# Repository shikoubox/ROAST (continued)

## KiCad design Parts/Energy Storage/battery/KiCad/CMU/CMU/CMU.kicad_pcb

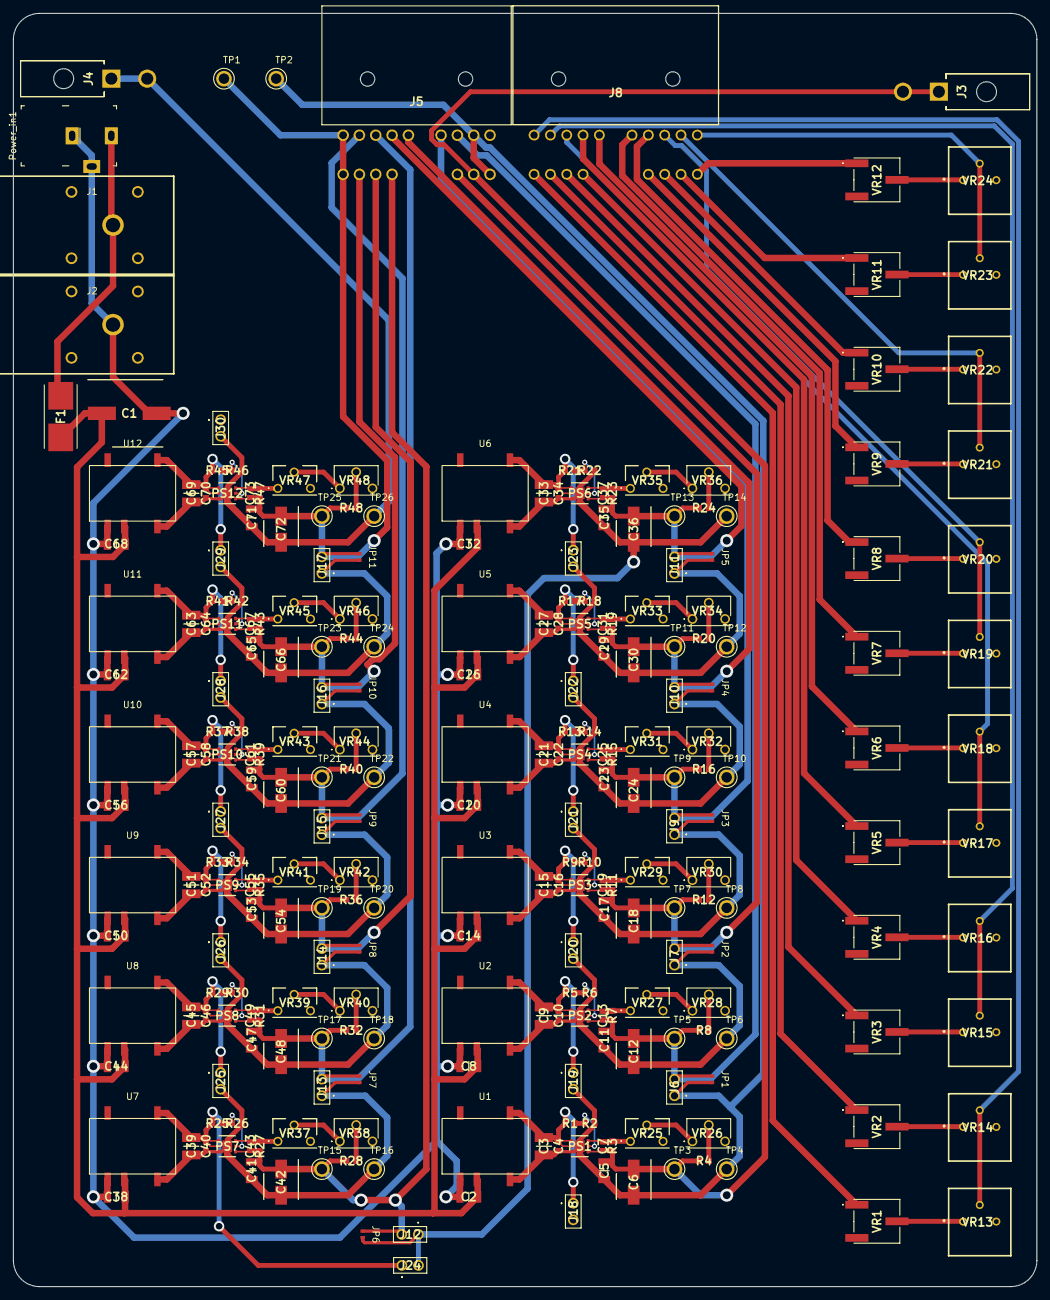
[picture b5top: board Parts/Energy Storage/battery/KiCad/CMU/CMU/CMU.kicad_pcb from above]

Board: 4 copper layers, 156.8 x 195.0 mm, 262 parts (0 on the bottom side), 117 nets.

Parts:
C1: 865080657018; CAPAE1030X1050N
C2, C8, C14, C20, C26, C32, C38, C44, C50, C56, C62, C68: 885012208094; CAPC3216X180N
C3, C9, C15, C21, C27, C33, C39, C45, C51, C57, C63, C69: 885012209073; CAPC3225X280N
C4, C10, C16, C22, C28, C34, C40, C46, C52, C58, C64, C70: 885012206095; CAPC1608X87N
C5, C11, C17, C23, C29, C35, C41, C47, C53, C59, C65, C71: 885012208069; CAPC3216X180N
C6, C12, C18, C24, C30, C36, C42, C48, C54, C60, C66, C72: 875105242010; CAPAE530X550N
C7, C13, C19, C25, C31, C37, C43, C49, C55, C61, C67, C73: 885012006053; CAPC1608X87N
F1: 015406.3DR; 0154063DR
J1, J2: FCR7350R
J3, J4: 649002227222
J5: IL-AG5-16P-D3L2-A; ILAG516PD3L2A
J6, J7, J9, J10, J11, J12, J13, J14, J15, J16, J17, J18, J19, J20, J21, J22, J23, J24, J25, J26, J27, J28, J29, J30: 77311-101-02LF; 7731110102LF
J8: IL-AG5-18P-D3L2; ILAG518PD3L2
JP1, JP2, JP3, JP4, JP5, JP6, JP7, JP8, JP9, JP10, JP11: SolderJumper_2_Open; solder_jumper
PS1, PS2, PS3, PS4, PS5, PS6, PS7, PS8, PS9, PS10, PS11, PS12: 171010502
Power_in1: PJ-102A; Barrel_Jack_5.5mmODx2.1mmID_PJ-102A
R1, R2, R3, R5, R6, R7, R9, R10, R11, R13, R14, R15, R17, R18, R19, R21, R22, R23, R25, R26, R27, R29, R30, R31, R33, R34, R35, R37, R38, R39, R41, R42, R43, R45, R46, R47: CRT0603-FZ-1003ELF; RESC1608X60N
R4, R8, R12, R16, R20, R24, R28, R32, R36, R40, R44, R48: RT0603FRE0720KL; RESC1608X55N
TP1, TP2, TP3, TP4, TP5, TP6, TP7, TP8, TP9, TP10, TP11, TP12, TP13, TP14, TP15, TP16, TP17, TP18, TP19, TP20, TP21, TP22, TP23, TP24, TP25, TP26: 5013; TESTPOINT_5013
U1, U2, U3, U4, U5, U6, U7, U8, U9, U10, U11, U12: 1769405341
VR1, VR2, VR3, VR4, VR5, VR6, VR7, VR8, VR9, VR10, VR11, VR12: 3361P-1-504GLF; 3361P1253GLF
VR13, VR14, VR15, VR16, VR17, VR18, VR19, VR20, VR21, VR22, VR23, VR24: 3362P-1-103TLF; 3296P-1-103
VR25, VR27, VR29, VR31, VR33, VR35, VR37, VR39, VR41, VR43, VR45, VR47: PV37W104C01B00
VR26, VR28, VR30, VR32, VR34, VR36, VR38, VR40, VR42, VR44, VR46, VR48: PV37W102C01B00

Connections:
/CMU1/IN+: C1.1, C2.1, C8.1, C14.1, C20.1, C26.1, C32.1, C38.1, C44.1, C50.1, C56.1, C62.1, C68.1, F1.2, U1.2 (+VIN), U2.2 (+VIN), U3.2 (+VIN), U4.2 (+VIN), U5.2 (+VIN), U6.2 (+VIN), U7.2 (+VIN), U8.2 (+VIN), U9.2 (+VIN), U10.2 (+VIN), U11.2 (+VIN), U12.2 (+VIN)
/CMU1/IN-: C1.2, C2.2, C8.2, C14.2, C20.2, C26.2, C32.2, C38.2, C44.2, C50.2, C56.2, C62.2, C68.2, J2.5, Power_in1.2, Power_in1.3, U1.1 (-VIN), U2.1 (-VIN), U3.1 (-VIN), U4.1 (-VIN), U5.1 (-VIN), U6.1 (-VIN), U7.1 (-VIN), U8.1 (-VIN), U9.1 (-VIN), U10.1 (-VIN), U11.1 (-VIN), U12.1 (-VIN)
/CMU1/ISO+: C3.1, C4.1, J18.1, PS1.4 (VIN), PS1.5 (EN), R1.1, U1.5 (+VOUT)
/CMU2/ISO+: C9.1, C10.1, J19.1, PS2.4 (VIN), PS2.5 (EN), R5.1, U2.5 (+VOUT)
/CMU2/OUT-: C9.2, C10.2, C11.2, C12.2, J7.1, J20.2, JP2.2 (B), PS2.6 (PGND), PS2.7 (EP), R6.2, TP6.1, U2.4 (-VOUT)
/CMU3/ISO+: C15.1, C16.1, J20.1, PS3.4 (VIN), PS3.5 (EN), R9.1, U3.5 (+VOUT)
/CMU3/OUT-: C15.2, C16.2, C17.2, C18.2, J9.1, J21.2, JP3.2 (B), PS3.6 (PGND), PS3.7 (EP), R10.2, TP8.1, U3.4 (-VOUT)
/CMU4/ISO+: C21.1, C22.1, J21.1, PS4.4 (VIN), PS4.5 (EN), R13.1, U4.5 (+VOUT)
/CMU4/OUT-: C21.2, C22.2, C23.2, C24.2, J10.1, J22.2, JP4.2 (B), PS4.6 (PGND), PS4.7 (EP), R14.2, TP10.1, U4.4 (-VOUT)
/CMU5/ISO+: C27.1, C28.1, J22.1, PS5.4 (VIN), PS5.5 (EN), R17.1, U5.5 (+VOUT)
/CMU5/OUT-: C27.2, C28.2, C29.2, C30.2, J11.1, J23.2, JP5.2 (B), PS5.6 (PGND), PS5.7 (EP), R18.2, TP12.1, U5.4 (-VOUT)
/CMU6/ISO+: C33.1, C34.1, J23.1, PS6.4 (VIN), PS6.5 (EN), R21.1, U6.5 (+VOUT)
/CMU6/OUT-: C33.2, C34.2, C35.2, C36.2, J12.1, J24.2, JP6.2 (B), PS6.6 (PGND), PS6.7 (EP), R22.2, TP14.1, U6.4 (-VOUT)
/CMU7/ISO+: C39.1, C40.1, J24.1, PS7.4 (VIN), PS7.5 (EN), R25.1, U7.5 (+VOUT)
/CMU7/OUT-: C39.2, C40.2, C41.2, C42.2, J13.1, J25.2, JP7.2 (B), PS7.6 (PGND), PS7.7 (EP), R26.2, TP16.1, U7.4 (-VOUT)
/CMU8/ISO+: C45.1, C46.1, J25.1, PS8.4 (VIN), PS8.5 (EN), R29.1, U8.5 (+VOUT)
/CMU8/OUT-: C45.2, C46.2, C47.2, C48.2, J14.1, J26.2, JP8.2 (B), PS8.6 (PGND), PS8.7 (EP), R30.2, TP18.1, U8.4 (-VOUT)
/CMU9/ISO+: C51.1, C52.1, J26.1, PS9.4 (VIN), PS9.5 (EN), R33.1, U9.5 (+VOUT)
/CMU9/OUT-: C51.2, C52.2, C53.2, C54.2, J15.1, J27.2, JP9.2 (B), PS9.6 (PGND), PS9.7 (EP), R34.2, TP20.1, U9.4 (-VOUT)
/CMU10/ISO+: C57.1, C58.1, J27.1, PS10.4 (VIN), PS10.5 (EN), R37.1, U10.5 (+VOUT)
/CMU10/OUT-: C57.2, C58.2, C59.2, C60.2, J16.1, J28.2, JP10.2 (B), PS10.6 (PGND), PS10.7 (EP), R38.2, TP22.1, U10.4 (-VOUT)
/CMU11/ISO+: C63.1, C64.1, J28.1, PS11.4 (VIN), PS11.5 (EN), R41.1, U11.5 (+VOUT)
/CMU11/OUT-: C63.2, C64.2, C65.2, C66.2, J17.1, J29.2, JP11.2 (B), PS11.6 (PGND), PS11.7 (EP), R42.2, TP24.1, U11.4 (-VOUT)
/CMU12/ISO+: C69.1, C70.1, J29.1, PS12.4 (VIN), PS12.5 (EN), R45.1, U12.5 (+VOUT)
/CMU12/ISO-: C69.2, C70.2, C71.2, C72.2, J4.1, J4.2, J30.2, PS12.6 (PGND), PS12.7 (EP), R46.2, TP26.1, U12.4 (-VOUT)
/GND_NTC_1_2: J8.18, VR23.2 (WIPER), VR24.2 (WIPER)
/GND_NTC_3_4: J8.17, VR21.2 (WIPER), VR22.2 (WIPER)
/GND_NTC_5_6: J8.16, VR19.2 (WIPER), VR20.2 (WIPER)
/GND_NTC_7_8: J8.11, VR17.2 (WIPER), VR18.2 (WIPER)
/GND_NTC_9_10: J8.10, VR15.2 (WIPER), VR16.2 (WIPER)
/GND_NTC_11_12: J8.9, VR13.2 (WIPER), VR14.2 (WIPER)
CMU1+: C5.1, C6.1, C7.1, J3.1, J3.2, J5.6, PS1.1 (VOUT), R3.2, R4.2, TP3.1
CMU1-: C3.2, C4.2, C5.2, C6.2, J5.7, J5.15, J6.1, J19.2, JP1.2 (B), PS1.6 (PGND), PS1.7 (EP), R2.2, TP2.1, TP4.1, U1.4 (-VOUT)
CMU2+: C11.1, C12.1, C13.1, J5.14, J6.2, JP1.1 (A), PS2.1 (VOUT), R7.2, R8.2, TP5.1
CMU3+: C17.1, C18.1, C19.1, J5.5, J7.2, JP2.1 (A), PS3.1 (VOUT), R11.2, R12.2, TP7.1
CMU4+: C23.1, C24.1, C25.1, J5.13, J9.2, JP3.1 (A), PS4.1 (VOUT), R15.2, R16.2, TP9.1
CMU5+: C29.1, C30.1, C31.1, J5.12, J10.2, JP4.1 (A), PS5.1 (VOUT), R19.2, R20.2, TP11.1
CMU6+: C35.1, C36.1, C37.1, J5.11, J11.2, JP5.1 (A), PS6.1 (VOUT), R23.2, R24.2, TP13.1
CMU7+: C41.1, C42.1, C43.1, J5.4, J12.2, JP6.1 (A), PS7.1 (VOUT), R27.2, R28.2, TP15.1
CMU8+: C47.1, C48.1, C49.1, J5.10, J13.2, JP7.1 (A), PS8.1 (VOUT), R31.2, R32.2, TP17.1
CMU9+: C53.1, C54.1, C55.1, J5.3, J14.2, JP8.1 (A), PS9.1 (VOUT), R35.2, R36.2, TP19.1
CMU10+: C59.1, C60.1, C61.1, J5.9, J15.2, JP9.1 (A), PS10.1 (VOUT), R39.2, R40.2, TP21.1
CMU11+: C65.1, C66.1, C67.1, J5.2, J16.2, JP10.1 (A), PS11.1 (VOUT), R43.2, R44.2, TP23.1
CMU12+: C71.1, C72.1, C73.1, J5.1, J5.8, J17.2, JP11.1 (A), PS12.1 (VOUT), R47.2, R48.2, TP1.1, TP25.1
unnamed: C7.2, PS1.3 (FB), R3.1, VR25.1 (CCW)
unnamed: C13.2, PS2.3 (FB), R7.1, VR27.1 (CCW)
unnamed: C19.2, PS3.3 (FB), R11.1, VR29.1 (CCW)
unnamed: C25.2, PS4.3 (FB), R15.1, VR31.1 (CCW)
unnamed: C31.2, PS5.3 (FB), R19.1, VR33.1 (CCW)
unnamed: C37.2, PS6.3 (FB), R23.1, VR35.1 (CCW)
unnamed: C43.2, PS7.3 (FB), R27.1, VR37.1 (CCW)
unnamed: C49.2, PS8.3 (FB), R31.1, VR39.1 (CCW)
unnamed: C55.2, PS9.3 (FB), R35.1, VR41.1 (CCW)
unnamed: C61.2, PS10.3 (FB), R39.1, VR43.1 (CCW)
unnamed: C67.2, PS11.3 (FB), R43.1, VR45.1 (CCW)
unnamed: C73.2, PS12.3 (FB), R47.1, VR47.1 (CCW)
unnamed: F1.1, J1.5, Power_in1.1
unnamed: J8.1, VR1.1 (CCW)
unnamed: J8.2, VR2.1 (CCW)
unnamed: J8.3, VR3.1 (CCW)
unnamed: J8.4, VR4.1 (CCW)
unnamed: J8.5, VR9.1 (CCW)
unnamed: J8.6, VR10.1 (CCW)
unnamed: J8.7, VR11.1 (CCW)
unnamed: J8.8, VR12.1 (CCW)
unnamed: J8.12, VR5.1 (CCW)
unnamed: J8.13, VR6.1 (CCW)
unnamed: J8.14, VR7.1 (CCW)
unnamed: J8.15, VR8.1 (CCW)
unnamed: PS1.2 (MODE), R1.2, R2.1
unnamed: PS2.2 (MODE), R5.2, R6.1
unnamed: PS3.2 (MODE), R9.2, R10.1
unnamed: PS4.2 (MODE), R13.2, R14.1
unnamed: PS5.2 (MODE), R17.2, R18.1
unnamed: PS6.2 (MODE), R21.2, R22.1
unnamed: PS7.2 (MODE), R25.2, R26.1
unnamed: PS8.2 (MODE), R29.2, R30.1
unnamed: PS9.2 (MODE), R33.2, R34.1
unnamed: PS10.2 (MODE), R37.2, R38.1
unnamed: PS11.2 (MODE), R41.2, R42.1
unnamed: PS12.2 (MODE), R45.2, R46.1
unnamed: R4.1, VR26.2 (WIPER)
unnamed: R8.1, VR28.2 (WIPER)
unnamed: R12.1, VR30.2 (WIPER)
unnamed: R16.1, VR32.2 (WIPER)
unnamed: R20.1, VR34.2 (WIPER)
unnamed: R24.1, VR36.2 (WIPER)
unnamed: R28.1, VR38.2 (WIPER)
unnamed: R32.1, VR40.2 (WIPER)
unnamed: R36.1, VR42.2 (WIPER)
unnamed: R40.1, VR44.2 (WIPER)
unnamed: R44.1, VR46.2 (WIPER)
unnamed: R48.1, VR48.2 (WIPER)
unnamed: VR1.2 (WIPER), VR13.1 (CCW)
unnamed: VR10.2 (WIPER), VR22.1 (CCW)
unnamed: VR11.2 (WIPER), VR23.1 (CCW)
unnamed: VR12.2 (WIPER), VR24.1 (CCW)
unnamed: VR2.2 (WIPER), VR14.1 (CCW)
unnamed: VR3.2 (WIPER), VR15.1 (CCW)
unnamed: VR4.2 (WIPER), VR16.1 (CCW)
unnamed: VR5.2 (WIPER), VR17.1 (CCW)
unnamed: VR6.2 (WIPER), VR18.1 (CCW)
unnamed: VR7.2 (WIPER), VR19.1 (CCW)
unnamed: VR8.2 (WIPER), VR20.1 (CCW)
unnamed: VR9.2 (WIPER), VR21.1 (CCW)
unnamed: VR25.2 (WIPER_), VR26.1 (CCW)
unnamed: VR27.2 (WIPER_), VR28.1 (CCW)
unnamed: VR29.2 (WIPER_), VR30.1 (CCW)
unnamed: VR31.2 (WIPER_), VR32.1 (CCW)
unnamed: VR33.2 (WIPER_), VR34.1 (CCW)
unnamed: VR35.2 (WIPER_), VR36.1 (CCW)
unnamed: VR37.2 (WIPER_), VR38.1 (CCW)
unnamed: VR39.2 (WIPER_), VR40.1 (CCW)
unnamed: VR41.2 (WIPER_), VR42.1 (CCW)
unnamed: VR43.2 (WIPER_), VR44.1 (CCW)
unnamed: VR45.2 (WIPER_), VR46.1 (CCW)
unnamed: VR47.2 (WIPER_), VR48.1 (CCW)

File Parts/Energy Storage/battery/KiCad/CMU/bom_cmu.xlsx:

Id | Designator | Package | Quantity | Designation | Manufacturer | Price/unit [€] | Total [€] | AVAL. ATTOW. | Link
1 | R32,R28,R8,R44,R40,R16,R48,R36,R12,R4,R20,R24 | RESC1608X55N | 12 | RT0603FRE0720KL | x | 1.6E-2 | 0.192 | 53684 | https://www.mouser.dk/ProductDetail/YAGEO/RT0603FRE0720KL?qs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
2 | H4,H1,H2,H3 | MountingHole_3.2mm_M3_ISO7380_Pad | 4 | MountingHole |  | 0 | 0 | PCB design
3 | VR27,VR33,VR41,VR39,VR37,VR1,VR47,VR35,VR31,VR29,VR45,VR43 | PV37W104C01B00 | 12 | PV37W104C01B00 | x | 1.57 | 18.84 | 19364 | https://www.mouser.dk/ProductDetail/Bourns/PV37W104C01B00?qs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
4 | VR25,VR22,VR15,VR17,VR26,VR23,VR24,VR19,VR21,VR18,VR20,VR16 | PV37W103C01B00 | 12 | PV37W103C01B00 | x | 1.58 | 18.96 | 2223 | https://www.mouser.dk/ProductDetail/Bourns/PV37W103C01B00?qs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
5 | JP3,JP7,JP5,JP8,JP10,JP11,JP9,JP6,JP1,JP4,JP2 | solder_jumper | 11 | SolderJumper_2_Open |  | 0 | 0 | PCB design
6 | J28,J19,J25,J5,J27,J10,J24,J26,J11,J6,J23,J14,J20,J9,J4,J12,J21,J22,J7,J16,J15,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 | 7731110102LF | 24 | 77311-101-02LF | x | 0.16500000000000001 | 3.96 | 5243 | https://www.mouser.dk/ProductDetail/Amphenol-FCI/77311-101-0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
7 | C3,C64,C52,C22,C40,C28,C16,C58,C10,C70,C46,C34 | CAPC1608X87N | 12 | 885012206095 | x | 5.2999999999999999E-2 | 0.63600000000000001 | 96611 | https://www.mouser.dk/ProductDetail/Wurth-Elektronik/8850122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
8 | C9,C39,C2,C51,C15,C21,C27,C33,C57,C63,C69,C45 | CAPC3225X280N | 12 | 885012209073 | x | 1.5920000000000001 | 19.103999999999999 | 1915 | https://www.digikey.dk/en/products/detail/w%C3%BCrth-elektro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
9 | TP14,TP21,TP40,TP13,TP48,TP16,TP10,TP17,TP34,TP53,TP5,TP44,TP22,TP36,TP54,TP15,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 | TESTPOINT_5013 | 62 | 5013 | x | 0.26700000000000002 | 16.554000000000002 | 28911 | https://www.mouser.dk/ProductDetail/Keystone-Electronics/501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
10 | R31,R25,R35,R23,R2,R29,R11,R21,R15,R30,R22,R43,R26,R45,R1,R3,R47,R33,R42,R41,R4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 | RESC1608X60N | 36 | MCT06030C1003FP500 | x | 4.3999999999999997E-2 | 1.5839999999999999 | 69865 | https://www.digikey.dk/en/products/detail/vishay-beyschlag-d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
11 | C26,C32,C8,C62,C1,C44,C20,C50,C38,C14,C56,C68 | CAPC3216X180N | 12 | 885012208094 | x | 0.79100000000000004 | 9.4920000000000009 | 7413 | https://www.digikey.dk/en/products/detail/w%C3%BCrth-elektro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
12 | VR28,VR2,VR44,VR34,VR36,VR38,VR46,VR32,VR42,VR48,VR40,VR30 | PV37W102C01B00 | 12 | PV37W102C01B00 | x | 1.52 | 18.240000000000002 | 2268 | https://www.mouser.dk/ProductDetail/Bourns/PV37W102C01B00?qs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
13 | U3,U1,U10,U7,U12,U5,U6,U9,U8,U4,U11,U2 | 1769405341 | 12 | 1769405341 | x | 6.1680000000000001 | 74.016000000000005 | 417 | https://www.mouser.dk/ProductDetail/Wurth-Elektronik/1769405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
14 | C11,C23,C35,C59,C71,C4,C65,C53,C29,C41,C47,C17 | CAPC3216X180N | 12 | 885012208069 | x | 0.50900000000000001 | 6.1080000000000005 | 18083 | https://www.digikey.dk/en/products/detail/w%C3%BCrth-elektro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
15 | C42,C24,C66,C18,C72,C30,C60,C36,C48,C12,C5,C54 | CAPAE530X550N | 12 | 875105242010 | x | 0.46899999999999997 | 5.6280000000000001 | 2312 | https://www.digikey.dk/en/products/detail/w%C3%BCrth-elektro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
16 | C7 | CAPAE1030X1050N | 1 | 865080657018 | Wurth Elektronik | 0.84 | 0.84 | 77987 | https://www.digikey.dk/en/products/detail/w%C3%BCrth-elektro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
17 | C13,C55,C6,C49,C67,C19,C43,C31,C25,C61,C37,C73 | CAPC1608X87N | 12 | 885012006053 | x | 2.4E-2 | 0.28800000000000003 | 15365 | https://www.mouser.dk/ProductDetail/Wurth-Elektronik/8850120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
18 | J18,J17 | 649002227222 | 2 | 649002227222 | Wurth Elektronik | 1.27 | 2.54 | 2337 | https://www.mouser.dk/ProductDetail/Wurth-Elektronik/6490022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
 |  |  | 2 | 649002113322 | x | 0.17 | 0.34 | 4482 | https://www.digikey.dk/en/products/detail/w%C3%BCrth-elektro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
19 | PS12,PS3,PS2,PS1,PS10,PS11,PS8,PS4,PS5,PS7,PS9,PS6 | 171010502 | 12 | 171010502 | x | 4.4779999999999998 | 53.735999999999997 | 620 | https://www.digikey.dk/en/products/detail/w%C3%BCrth-elektro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
20 | VR6,VR7,VR12,VR4,VR3,VR9,VR5,VR14,VR11,VR13,VR8,VR10 | PV37W504C01B00 | 12 | PV37W504C01B00 | x | 0.81 | 9.7200000000000006 | 1755 | https://www.mouser.dk/ProductDetail/Bourns/PV37W504C01B00?qs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
21 | J3 | FCR7350B | 1 | FCR7350B | x | 4.8499999999999996 | 4.8499999999999996 | 806 | https://www.digikey.dk/en/products/detail/cliff-electronic-c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
22 | J1 | FCR7350R | 1 | FCR7350R | x | 4.8499999999999996 | 4.8499999999999996 | 5587 | https://www.digikey.dk/en/products/detail/cliff-electronic-c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
23 | Power_in1 | Barrel_Jack_5.5mmODx2.1mmID_PJ-102A | 1 | PJ-102A | x | 0.60499999999999998 | 0.60499999999999998 | 17619 | https://www.mouser.dk/ProductDetail/CUI-Devices/PJ-102A?qs=W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
24 | J2 | 64901629522 | 1 | 64901629522 | x | 1.87 | 1.87 | 90 | https://www.digikey.dk/en/products/detail/w%C3%BCrth-elektro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
 |  |  | 1 | 649016113322 | x | 0.63 | 0.63 | 315 | https://www.digikey.dk/en/products/detail/w%C3%BCrth-elektro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
25 | F1 | 0154063DR | 1 | 015406.3DR | x | 2.5 | 2.5 | 7949 | https://www.mouser.dk/ProductDetail/Littelfuse/015406.3DR?qs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
 |  |  | 5 | 045106.3MRL | x | 1.266 | 6.33 | 782 | https://www.digikey.dk/en/products/detail/littelfuse-inc/045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
26 | J30 | 64901829522 | 1 | 64901829522 | x | 1.99 | 1.99 | 63 | https://www.digikey.dk/en/products/detail/w%C3%BCrth-elektro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
 |  |  | 1 | 649018113322 | x | 0.7 | 0.7 | 140 | https://www.digikey.dk/en/products/detail/w%C3%BCrth-elektro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
 |  |  |  |  |  | Total | 285.10300000000007

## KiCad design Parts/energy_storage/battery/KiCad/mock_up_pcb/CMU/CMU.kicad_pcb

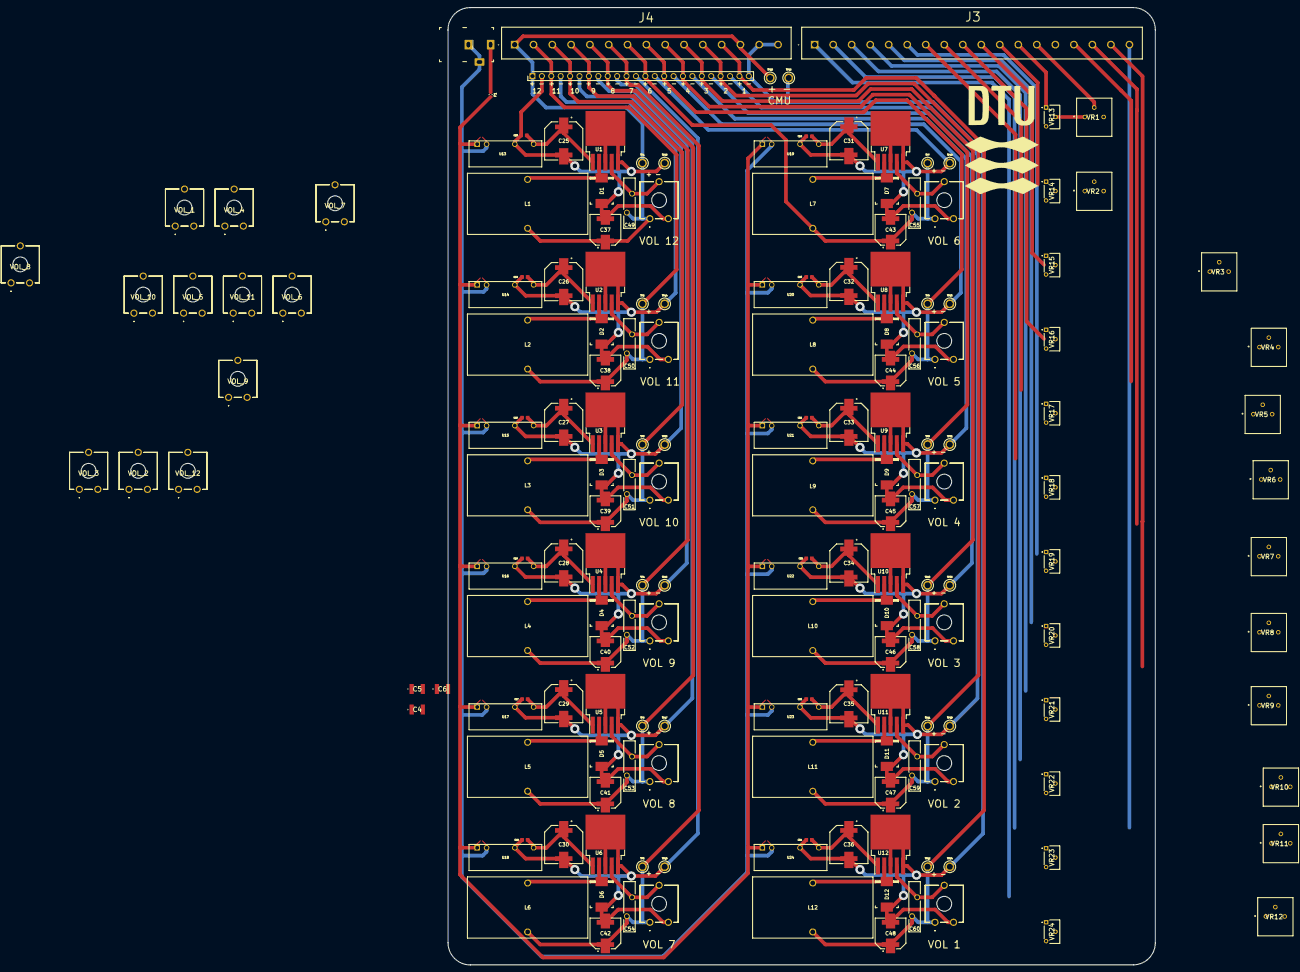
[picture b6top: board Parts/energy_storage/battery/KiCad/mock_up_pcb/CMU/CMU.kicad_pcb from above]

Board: 2 copper layers, 191.0 x 258.5 mm, 178 parts (0 on the bottom side), 93 nets.

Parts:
C4, C5, C6: C1210C225K1RACAUTO; C1210
C13, C14, C15, C16, C17, C18, C19, C20, C21, C22, C23, C24: 10u; CAPC1608X100N
C25, C26, C27, C28, C29, C30, C31, C32, C33, C34, C35, C36: 470u; CAP_EEETP1A471AV
C37, C38, C39, C40, C41, C42, C43, C44, C45, C46, C47, C48: 220u; CAP_EEETP1A221AV
C49, C50, C51, C52, C53, C54, C55, C56, C57, C58, C59, C60: 3.2n; FUSRB510W81L1358T310H1980
D1, D2, D3, D4, D5, D6, D7, D8, D9, D10, D11, D12: B540C-13-F; DO-214AB
F1: 0ABB-5000-TM; FUSE_0ABB-5000-TM
J3: 1755668
J4: 1755862
L1, L2, L3, L4, L5, L6, L7, L8, L9, L10, L11, L12: HCTI-100-7.0; IND_HCTI-68-7.7
Power_in1: PJ-102A; Barrel_Jack_5.5mmODx2.1mmID_PJ-102A
TP1, TP2, TP3, TP4, TP5, TP6, TP7, TP8, TP9, TP10, TP11, TP12, TP13, TP14, TP15, TP16, TP17, TP18, TP19, TP20, TP21, TP22, TP23, TP24, TP25, TP26: 5013; TESTPOINT_5013
U1, U2, U3, U4, U5, U6, U7, U8, U9, U10, U11, U12: LM2596S-ADJ; TO-263-5_TabPin3
U13, U14, U15, U16, U17, U18, U19, U20, U21, U22, U23, U24: PEM2-S12-S5-S; CONV_PEM2-S12-S5-S
VOL 1, VOL 2, VOL 3, VOL 4, VOL 5, VOL 6, VOL 7, VOL 8, VOL 9, VOL 10, VOL 11, VOL 12: PT10RV10-103A2020-PM-S; PT10RV10103A2020PMS
VOL_1, VOL_2, VOL_3, VOL_4, VOL_5, VOL_6, VOL_7, VOL_8, VOL_9, VOL_10, VOL_11, VOL_12: PT10RV10-103A2020-PM-S; PT10RV10103A2020PMS
VR1, VR2, VR3, VR4, VR5, VR6, VR7, VR8, VR9, VR10, VR11, VR12: 3362P-1-103TLF; 3296P-1-103
VR13, VR14, VR15, VR16, VR17, VR18, VR19, VR20, VR21, VR22, VR23, VR24: 64WR500KLF
Voltage_headers1: 77311-102-24LF; HDRV24W62P0X254_1X24_6096X240X858P

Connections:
/CMU_vol_1: C48.1, C60.2, J4.12, L12.2, TP12.1, VOL 1.A1 (CCW), VOL_1.A1 (CCW), Voltage_headers1.23
/CMU_vol_2: C47.1, C59.2, J4.11, L11.2, TP11.1, VOL 2.A1 (CCW), VOL_2.A1 (CCW), Voltage_headers1.21
/CMU_vol_3: C46.1, C58.2, J4.10, L10.2, TP10.1, VOL 3.A1 (CCW), VOL_3.A1 (CCW), Voltage_headers1.19
/CMU_vol_4: C45.1, C57.2, J4.9, L9.2, TP9.1, VOL 4.A1 (CCW), VOL_4.A1 (CCW), Voltage_headers1.17
/CMU_vol_5: C44.1, C56.2, J4.8, L8.2, TP8.1, VOL 5.A1 (CCW), VOL_5.A1 (CCW), Voltage_headers1.15
/CMU_vol_6: C43.1, C55.2, J4.7, L7.2, TP7.1, VOL 6.A1 (CCW), VOL_6.A1 (CCW), Voltage_headers1.13
/CMU_vol_7: C42.1, C54.2, J4.6, L6.2, TP6.1, VOL 7.A1 (CCW), VOL_7.A1 (CCW), Voltage_headers1.11
/CMU_vol_8: C41.1, C53.2, J4.5, L5.2, TP5.1, VOL 8.A1 (CCW), VOL_8.A1 (CCW), Voltage_headers1.9
/CMU_vol_9: C40.1, C52.2, J4.4, L4.2, TP4.1, VOL 9.A1 (CCW), VOL_9.A1 (CCW), Voltage_headers1.7
/CMU_vol_10: C39.1, C51.2, J4.3, L3.2, TP3.1, VOL 10.A1 (CCW), VOL_10.A1 (CCW), Voltage_headers1.5
/CMU_vol_11: C38.1, C50.2, J4.2, L2.2, TP2.1, VOL 11.A1 (CCW), VOL_11.A1 (CCW), Voltage_headers1.3
/CMU_vol_12: C37.1, C49.2, J4.1, J4.13, L1.2, TP1.1, TP25.1, VOL 12.A1 (CCW), VOL_12.A1 (CCW), Voltage_headers1.1
/GND_NTC_1_2: J3.18, VR11.2 (WIPER), VR12.2 (WIPER)
/GND_NTC_3_4: J3.17, VR9.2 (WIPER), VR10.2 (WIPER)
/GND_NTC_5_6: J3.16, VR7.2 (WIPER), VR8.2 (WIPER)
/GND_NTC_7_8: J3.15, VR5.2 (WIPER), VR6.2 (WIPER)
/GND_NTC_9_10: J3.14, VR3.2 (WIPER), VR4.2 (WIPER)
/GND_NTC_11_12: J3.13, VR1.2 (WIPER), VR2.2 (WIPER)
/VOL_1-: C24.2, C36.2, C48.2, D12.A, J4.14, J4.15, TP24.1, TP26.1, U12.3 (GND), U12.5 (~ON/OFF), U24.5 (0V), VOL 1.E1 (CW), VOL_1.E1 (CW), Voltage_headers1.24
GND: C4.2, C5.2, C6.2, Power_in1.2, Power_in1.3, U13.2 (GND), U14.2 (GND), U15.2 (GND), U16.2 (GND), U17.2 (GND), U18.2 (GND), U19.2 (GND), U20.2 (GND), U21.2 (GND), U22.2 (GND), U23.2 (GND), U24.2 (GND)
unnamed: C13.1, C25.1, U1.1 (VIN), U13.7 (+VO)
unnamed: C13.2, C25.2, C37.2, D1.A, TP13.1, U1.3 (GND), U1.5 (~ON/OFF), U13.5 (0V), VOL 12.E1 (CW), VOL_12.E1 (CW), Voltage_headers1.2
unnamed: C14.1, C26.1, U2.1 (VIN), U14.7 (+VO)
unnamed: C14.2, C26.2, C38.2, D2.A, TP14.1, U2.3 (GND), U2.5 (~ON/OFF), U14.5 (0V), VOL 11.E1 (CW), VOL_11.E1 (CW), Voltage_headers1.4
unnamed: C15.1, C27.1, U3.1 (VIN), U15.7 (+VO)
unnamed: C15.2, C27.2, C39.2, D3.A, TP15.1, U3.3 (GND), U3.5 (~ON/OFF), U15.5 (0V), VOL 10.E1 (CW), VOL_10.E1 (CW), Voltage_headers1.6
unnamed: C16.1, C28.1, U4.1 (VIN), U16.7 (+VO)
unnamed: C16.2, C28.2, C40.2, D4.A, TP16.1, U4.3 (GND), U4.5 (~ON/OFF), U16.5 (0V), VOL 9.E1 (CW), VOL_9.E1 (CW), Voltage_headers1.8
unnamed: C17.1, C29.1, U5.1 (VIN), U17.7 (+VO)
unnamed: C17.2, C29.2, C41.2, D5.A, TP17.1, U5.3 (GND), U5.5 (~ON/OFF), U17.5 (0V), VOL 8.E1 (CW), VOL_8.E1 (CW), Voltage_headers1.10
unnamed: C18.1, C30.1, U6.1 (VIN), U18.7 (+VO)
unnamed: C18.2, C30.2, C42.2, D6.A, TP18.1, U6.3 (GND), U6.5 (~ON/OFF), U18.5 (0V), VOL 7.E1 (CW), VOL_7.E1 (CW), Voltage_headers1.12
unnamed: C19.1, C31.1, U7.1 (VIN), U19.7 (+VO)
unnamed: C19.2, C31.2, C43.2, D7.A, TP19.1, U7.3 (GND), U7.5 (~ON/OFF), U19.5 (0V), VOL 6.E1 (CW), VOL_6.E1 (CW), Voltage_headers1.14
unnamed: C20.1, C32.1, U8.1 (VIN), U20.7 (+VO)
unnamed: C20.2, C32.2, C44.2, D8.A, TP20.1, U8.3 (GND), U8.5 (~ON/OFF), U20.5 (0V), VOL 5.E1 (CW), VOL_5.E1 (CW), Voltage_headers1.16
unnamed: C21.1, C33.1, U9.1 (VIN), U21.7 (+VO)
unnamed: C21.2, C33.2, C45.2, D9.A, TP21.1, U9.3 (GND), U9.5 (~ON/OFF), U21.5 (0V), VOL 4.E1 (CW), VOL_4.E1 (CW), Voltage_headers1.18
unnamed: C22.1, C34.1, U10.1 (VIN), U22.7 (+VO)
unnamed: C22.2, C34.2, C46.2, D10.A, TP22.1, U10.3 (GND), U10.5 (~ON/OFF), U22.5 (0V), VOL 3.E1 (CW), VOL_3.E1 (CW), Voltage_headers1.20
unnamed: C23.1, C35.1, U11.1 (VIN), U23.7 (+VO)
unnamed: C23.2, C35.2, C47.2, D11.A, TP23.1, U11.3 (GND), U11.5 (~ON/OFF), U23.5 (0V), VOL 2.E1 (CW), VOL_2.E1 (CW), Voltage_headers1.22
unnamed: C24.1, C36.1, U12.1 (VIN), U24.7 (+VO)
unnamed: C49.1, U1.4 (FB), VOL 12.S1 (WIPER), VOL_12.S1 (WIPER)
unnamed: C50.1, U2.4 (FB), VOL 11.S1 (WIPER), VOL_11.S1 (WIPER)
unnamed: C51.1, U3.4 (FB), VOL 10.S1 (WIPER), VOL_10.S1 (WIPER)
unnamed: C52.1, U4.4 (FB), VOL 9.S1 (WIPER), VOL_9.S1 (WIPER)
unnamed: C53.1, U5.4 (FB), VOL 8.S1 (WIPER), VOL_8.S1 (WIPER)
unnamed: C54.1, U6.4 (FB), VOL 7.S1 (WIPER), VOL_7.S1 (WIPER)
unnamed: C55.1, U7.4 (FB), VOL 6.S1 (WIPER), VOL_6.S1 (WIPER)
unnamed: C56.1, U8.4 (FB), VOL 5.S1 (WIPER), VOL_5.S1 (WIPER)
unnamed: C57.1, U9.4 (FB), VOL 4.S1 (WIPER), VOL_4.S1 (WIPER)
unnamed: C58.1, U10.4 (FB), VOL 3.S1 (WIPER), VOL_3.S1 (WIPER)
unnamed: C59.1, U11.4 (FB), VOL 2.S1 (WIPER), VOL_2.S1 (WIPER)
unnamed: C60.1, U12.4 (FB), VOL 1.S1 (WIPER), VOL_1.S1 (WIPER)
unnamed: D1.K, L1.1, U1.2 (OUT)
unnamed: D2.K, L2.1, U2.2 (OUT)
unnamed: D3.K, L3.1, U3.2 (OUT)
unnamed: D4.K, L4.1, U4.2 (OUT)
unnamed: D5.K, L5.1, U5.2 (OUT)
unnamed: D6.K, L6.1, U6.2 (OUT)
unnamed: D7.K, L7.1, U7.2 (OUT)
unnamed: D8.K, L8.1, U8.2 (OUT)
unnamed: D9.K, L9.1, U9.2 (OUT)
unnamed: D10.K, L10.1, U10.2 (OUT)
unnamed: D11.K, L11.1, U11.2 (OUT)
unnamed: D12.K, L12.1, U12.2 (OUT)
unnamed: F1.1, Power_in1.1
unnamed: C4.1, C5.1, C6.1, F1.2, U13.1 (VIN), U14.1 (VIN), U15.1 (VIN), U16.1 (VIN), U17.1 (VIN), U18.1 (VIN), U19.1 (VIN), U20.1 (VIN), U21.1 (VIN), U22.1 (VIN), U23.1 (VIN), U24.1 (VIN)
unnamed: J3.1, VR24.1 (CCW)
unnamed: J3.2, VR23.1 (CCW)
unnamed: J3.3, VR22.1 (CCW)
unnamed: J3.4, VR21.1 (CCW)
unnamed: J3.5, VR20.1 (CCW)
unnamed: J3.6, VR19.1 (CCW)
unnamed: J3.7, VR18.1 (CCW)
unnamed: J3.8, VR17.1 (CCW)
unnamed: J3.9, VR16.1 (CCW)
unnamed: J3.10, VR15.1 (CCW)
unnamed: J3.11, VR14.1 (CCW)
unnamed: J3.12, VR13.1 (CCW)
unnamed: VR1.1 (CCW), VR13.2 (WIPER)
unnamed: VR2.1 (CCW), VR14.2 (WIPER)
unnamed: VR3.1 (CCW), VR15.2 (WIPER)
unnamed: VR4.1 (CCW), VR16.2 (WIPER)
unnamed: VR5.1 (CCW), VR17.2 (WIPER)
unnamed: VR6.1 (CCW), VR18.2 (WIPER)
unnamed: VR7.1 (CCW), VR19.2 (WIPER)
unnamed: VR8.1 (CCW), VR20.2 (WIPER)
unnamed: VR9.1 (CCW), VR21.2 (WIPER)
unnamed: VR10.1 (CCW), VR22.2 (WIPER)
unnamed: VR11.1 (CCW), VR23.2 (WIPER)
unnamed: VR12.1 (CCW), VR24.2 (WIPER)
